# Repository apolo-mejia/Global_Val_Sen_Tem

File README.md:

# Global_Val_Sen_Tem
Temperature module Sensor to for Microcontrolles , in the scope of Syracuza proyect. 
Features:
<ul>up
<li> Analog Outoput,</li>
<li> Digital Output via I2C BUS,</li>
<li> + 3 Analog Inputs to High Presicion ADC,</li>
<li> from -80°C to 1400° (optimized for 0°C to 340°C),</li>
<li> Isoated transitor alarm, </li>
<li> Cold point compensation </li>
<li> Compatible with K-type termocouples.</li>
<ul>

Side 4 of a Global Var sensor.<br>
 <br>
Next commitment: BOM, assembly

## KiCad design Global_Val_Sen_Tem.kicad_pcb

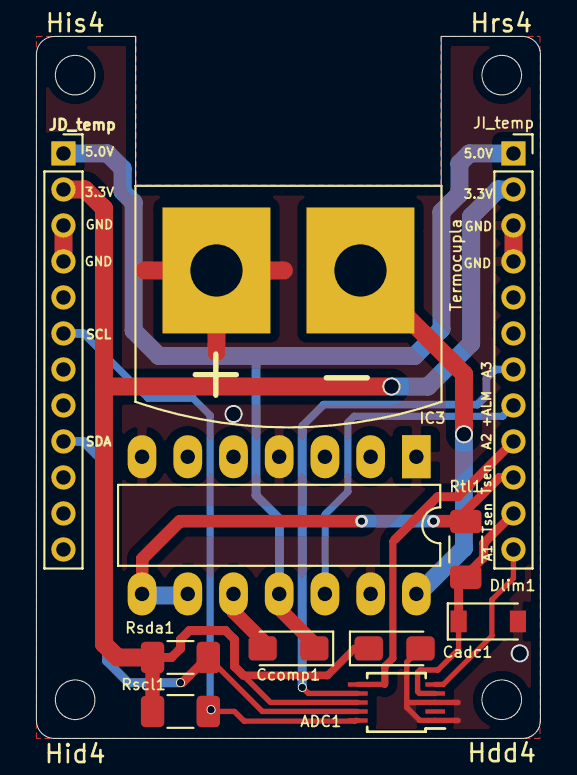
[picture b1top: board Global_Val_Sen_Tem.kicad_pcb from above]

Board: 2 copper layers, 28.0 x 39.0 mm, 15 parts (0 on the bottom side), 13 nets.

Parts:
ADC1: ADS1115IDGS; TSSOP-10_3x3mm_P0.5mm
Cadc1: 100n; CP_EIA-3216-10_Kemet-I_Pad1.58x1.35mm_HandSolder
Ccomp1: 10u; CP_EIA-3216-10_Kemet-I_Pad1.58x1.35mm_HandSolder
Dlim1: MMSD4148; D_SOD-123
Hdd4: MH; MountingHole_2.2mm_M2_DIN965
Hid4: MH; MountingHole_2.2mm_M2_DIN965
His4: MH; MountingHole_2.2mm_M2_DIN965
Hrs4: MH; MountingHole_2.2mm_M2_DIN965
IC3: AD595; DIP-14_W7.62mm_LongPads
JD_temp: Conn_01x12; PinSocket_1x12_P2.00mm_Vertical
JI_temp: Conn_01x12; PinSocket_1x12_P2.00mm_Vertical
Rscl1: 10k; R_1206_3216Metric_Pad1.30x1.75mm_HandSolder
Rsda1: 10k; R_1206_3216Metric_Pad1.30x1.75mm_HandSolder
Rtl1: 10k; R_1206_3216Metric_Pad1.30x1.75mm_HandSolder
Termocupla: Conn_01x02; thrmoK-F

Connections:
+3V3: ADC1.8, Cadc1.1, JD_temp.2, JI_temp.2, Rscl1.2, Rsda1.2
+5V: Ccomp1.1, IC3.11, JD_temp.1, JI_temp.1
+ALM: IC3.12, JI_temp.8
AIN1: ADC1.5, JI_temp.12
AIN2: ADC1.6, JI_temp.9
AIN3: ADC1.7, JI_temp.7
GND: ADC1.1, ADC1.3, Cadc1.2, Dlim1.2, IC3.1, IC3.4, IC3.7, IC3.13, JD_temp.3, JD_temp.4, JI_temp.3, JI_temp.4, Termocupla.1
unnamed: Ccomp1.2, IC3.10
unnamed: IC3.14, Termocupla.2
SCL0: ADC1.10, JD_temp.6, Rscl1.1
SDA0: ADC1.9, JD_temp.9, Rsda1.1
Tout: IC3.8, IC3.9, JI_temp.10, Rtl1.2
Tsen: ADC1.4, Dlim1.1, JI_temp.11, Rtl1.1

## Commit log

2023-01-13 upload image and schematic
